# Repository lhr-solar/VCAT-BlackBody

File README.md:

# VCAT-BlackBody

Blackbody sensor boards for the LHR solar car top shell (VCAT / Telemetry).

Measures **solar irradiance** and **solar-module temperature** at locations across the top shell and reports them over CAN.

## Boards

| Board | Folder | Purpose |
|---|---|---|
| Main board | `hardware/` (`BlackBodyBoard.kicad_pro`) | Collects sensor data from the breakout(s), does the math, sends CAN messages |
| Breakout board | `hardware/IrradianceBreakout` | Holds the irradiance and temperature sensors on the top shell |

Baseline quantity: 3 (final count and placement TBD).

## CAN data (planned)

| Message | Rate |
|---|---|
| Solar irradiance (W/m²) | 10 Hz |
| Solar-module temperature (°C) | 2 Hz |
| Board status / faults | 1 Hz |

## Repo layout

Same layout as VCAT-StrainGaugeBoard:

```
CubeMX/CubeMX.ioc               STM32G473 pin/clock config (started from strain gauge; re-pin for Blackbody)
hardware/BlackBodyBoard.*        main board project (root sheet)
hardware/<Block>.kicad_sch       design blocks: PowerProtection, 12VBuck, Power_Mux, LDO,
                                 USB-C_Connector, 48PinMCU, CAN_Transceiver,
                                 Irradiance, Thermocouple, TC_Channel
hardware/IrradianceBreakout/     sensor breakout project
lib/KiCAD-Sharepoint/            shared LHRS symbols, footprints, design blocks (submodule)
lib/footprints/, lib/3dmodels/   board-specific parts
```

Conventions: power symbols + local labels on the root sheet, hierarchical labels inside sub-sheets, inputs on the left / outputs on the right, passive values without units (`10k`, `0.1u`).

## Getting started

```sh
git clone https://github.com/lhr-solar/VCAT-BlackBody.git
cd VCAT-BlackBody
git submodule update --init --recursive
```

## Documentation

Requirements: VCAT Board Tracker → Blackbody Board (Notion).

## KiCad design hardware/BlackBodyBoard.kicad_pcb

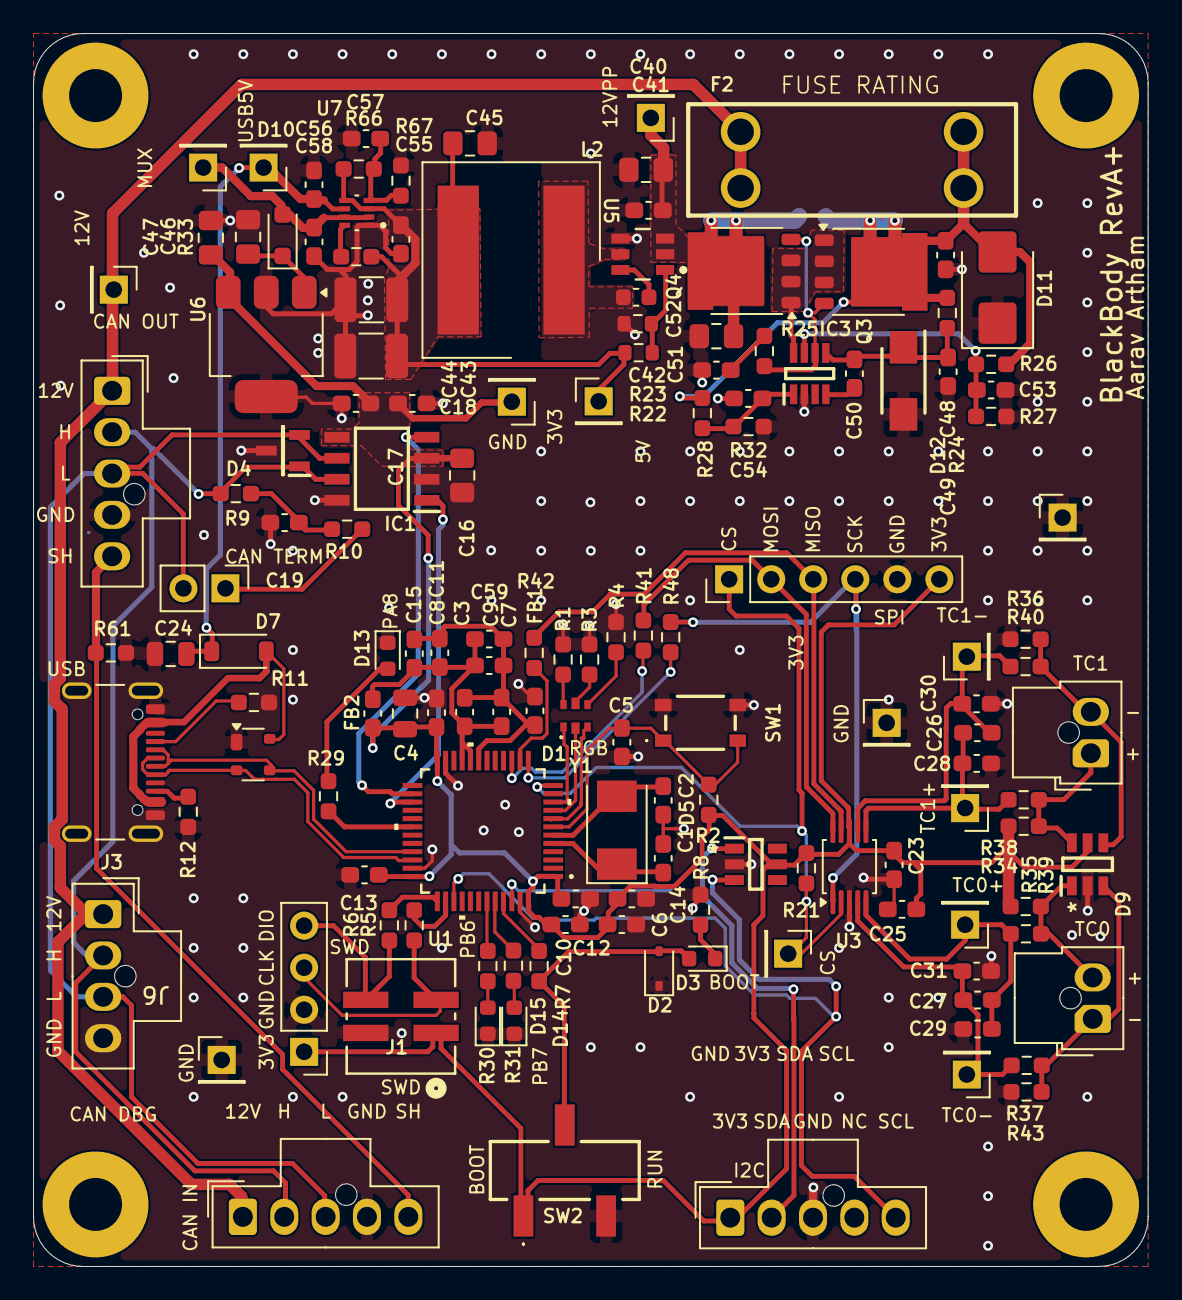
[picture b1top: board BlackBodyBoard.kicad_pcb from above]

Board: 2 copper layers, 67.3 x 74.5 mm, 147 parts (1 on the bottom side), 74 nets.

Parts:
C1, C2: 26p; C_0603_1608Metric_Pad1.08x0.95mm_HandSolder
C3, C5, C6, C7, C8, C10, C12, C13, C14, C17, C18, C19, C48, C53, C54, C55, C56, C57, C58: 0.1u; C_0603_1608Metric_Pad1.08x0.95mm_HandSolder
C4, C24: 10u; C_0805_2012Metric
C9, C11, C25, C49: 1u; C_0603_1608Metric_Pad1.08x0.95mm_HandSolder
C15, C23, C26, C27, C41: 100n; C_0603_1608Metric_Pad1.08x0.95mm_HandSolder
C16, C46, C47, C52: 10u; C_0805_2012Metric_Pad1.18x1.45mm_HandSolder
C28, C29, C30, C31, C51: 10n; C_0603_1608Metric_Pad1.08x0.95mm_HandSolder
C40: 4.7u; C_0805_2012Metric_Pad1.18x1.45mm_HandSolder
C42: 100n; C_0603_1608Metric
C43, C44: 22u; C_1210_3225Metric_Pad1.33x2.70mm_HandSolder
C45: 3.3u; C_0805_2012Metric_Pad1.18x1.45mm_HandSolder
C50: 220n; C_0603_1608Metric_Pad1.08x0.95mm_HandSolder
C59: 10u; C_0603_1608Metric_Pad1.08x0.95mm_HandSolder
D1: RGB_LED
D2: TVS; D_SOD-323
D3, D13, D14, D15: LED; LED_0603_1608Metric
D4: CDSOT23-T24CAN
D5, D9: D5V0P4UR6SO-7
D6: SP0503BAHT; SOT-143
D7: D_Schottky; D_SOD-123
D10: SBA130CH-AU_R1_000A1; D_SOD-323_HandSoldering
D11: SMBJ15CA; D_SMB
D12: SMAF4758A; SODFL5026X125N
F2: Fuse; Fuse-3557-2
FB1, FB2: FerriteBead; C_0603_1608Metric_Pad1.08x0.95mm_HandSolder
H1, H2, H3, H4: MountingHole_3.2mm_M3_Pad
IC1: TCAN3413DR
IC3: LM74502DDFR
J1: SWD_Header; SWD_Conn
J2: SWD; PinHeader_1x04_P2.54mm_Vertical
J3: USB_C_Receptacle_USB2.0_16P; USB_C_Receptacle_GCT_USB4105-xx-A_16P_TopMnt_Horizontal
J4: Nano-Fit 1x5; Molex_Nano-Fit_105309-xx05_1x05_P2.50mm_Vertical
J5, J8: TC K-type; Molex_Nano-Fit_105309-xx02_1x02_P2.50mm_Vertical
J6: CAN_DEBUG; Molex_Nano-Fit_105309-xx04_1x04_P2.50mm_Vertical
J7: CAN_IN; Molex_Nano-Fit_105309-xx05_1x05_P2.50mm_Vertical
J10: SPI; PinHeader_1x06_P2.54mm_Vertical
J11: CAN_OUT; Molex_Nano-Fit_105309-xx05_1x05_P2.50mm_Vertical
JP1: TRM; PinHeader_1x02_P2.54mm_Vertical
JP3: SolderJumper_2_Open; SolderJumper-2_P1.3mm_Open_RoundedPad1.0x1.5mm
L2: 8.2u; 74439369082
Q3, Q4: PSMN012-100YS; LFPAK56
R1, R3, R4, R8, R29, R30, R31, R38, R39, R40, R43: 1k; R_0603_1608Metric_Pad0.98x0.95mm_HandSolder
R2, R7, R21, R24, R33: 10k; R_0603_1608Metric_Pad0.98x0.95mm_HandSolder
R5, R6, R41, R42, R48: 22; R_0603_1608Metric_Pad0.98x0.95mm_HandSolder
R9, R10: 60; R_0603_1608Metric_Pad0.98x0.95mm_HandSolder
R11, R12: 5.1k; R_0603_1608Metric_Pad0.98x0.95mm_HandSolder
R22: 100k; R_0603_1608Metric
R23: 19.1k; R_0603_1608Metric
R25: 33; R_0603_1608Metric_Pad0.98x0.95mm_HandSolder
R26, R28: 100k; R_0603_1608Metric_Pad0.98x0.95mm_HandSolder
R27: 7.32k; R_0603_1608Metric_Pad0.98x0.95mm_HandSolder
R32: 15.8k; R_0603_1608Metric_Pad0.98x0.95mm_HandSolder
R34, R35, R36, R37: 1M; R_0603_1608Metric_Pad0.98x0.95mm_HandSolder
R61: 0; R_0603_1608Metric_Pad0.98x0.95mm_HandSolder
R66: 16k; R_0603_1608Metric_Pad0.98x0.95mm_HandSolder
R67: 4.7k; R_0603_1608Metric_Pad0.98x0.95mm_HandSolder
SW1: Reset; TL3365AF180QG
SW2: SW_SPDT; BootSW
TP6: TC_ADC_CS; PinHeader_1x01_P2.54mm_Vertical
TP7, TP8: TCP; PinHeader_1x01_P2.54mm_Vertical
TP10, TP11: TCN; PinHeader_1x01_P2.54mm_Vertical
TP38: +12V; PinHeader_1x01_P2.54mm_Vertical
TP39: +12V_PP; PinHeader_1x01_P2.54mm_Vertical
TP40: +5V_BUCK; PinHeader_1x01_P2.54mm_Vertical
TP41: +USBC_5V; PinHeader_1x01_P2.54mm_Vertical
TP42: MUX_OUT; PinHeader_1x01_P2.54mm_Vertical
TP44: Power TestPoint; PinHeader_1x01_P2.54mm_Vertical
TP45: MCU TestPoint; PinHeader_1x01_P2.54mm_Vertical
TP46: CAN TestPoint; PinHeader_1x01_P2.54mm_Vertical
TP_3.3V2: 3.3V; PinHeader_1x01_P2.54mm_Vertical
U1: STM32G473CETx; 48PinMCU
U3: ADS1118IDGS; TSSOP-10_3x3mm_P0.5mm
U5: LMR51635XDDCR; DDC0006A-MFG
U6: MCP1826S; SOT-223-3_TabPin2
U7: TPS2117DRLR
Y1: Crystal; Crystal_SMD_Abracon_ABM3-2Pin_5.0x3.2mm

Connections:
+3.3V: C4.1, C6.1, C8.1, C10.1, C12.1, C13.1, C14.1, C16.1, C17.1, C18.1, C23.1, C25.1, C47.2, D5.5, D9.5, FB2.1, IC1.3 (VCC), IC1.5 (SHDNV_IO), J1.1, J2.1, J4.1, J10.6, R2.2, R21.1, R34.1, R35.1, SW2.1 (A), TP_3.3V2.1 (1_1), U1.1 (VBAT), U1.24 (VDD), U1.36 (VDD), U1.48 (VDD), U3.8 (VDD), U6.3 (VO)
+12V: F2.1, J6.1 (12V), J7.1 (12V), J11.1 (12V), TP38.1 (1_1)
/12VBuck1/CB: C42.1, U5.6 (CB)
/12VBuck1/FB: R22.2, R23.1, U5.1 (FB)
/12VBuck1/SW: C42.2, L2.1, U5.5 (SW)
/48PinMCU/BOOT0: R7.1, U1.45 (PB8-BOOT0)
/48PinMCU/NRST: C5.1, R2.1, SW1.1, U1.7 (PG10-NRST)
/48PinMCU/PA0: D1.5, U1.8 (PA0-GPIO_BLUE)
/48PinMCU/PA1: D1.3, U1.9 (PA1_GPIO_RED)
/48PinMCU/PA2: D1.1, U1.10 (PA2-GPIO_GREEN)
/48PinMCU/PA5: R48.1, U1.13 (PA5)
/48PinMCU/PA6: R42.1, U1.14 (PA6)
/48PinMCU/PA7: R41.1, U1.15 (PA7)
/48PinMCU/PA8: R29.1, U1.30 (PA8)
/48PinMCU/PB6: R30.1, U1.43 (PB6)
/48PinMCU/PB7: R31.1, U1.44 (PB7)
/48PinMCU/SWCLK: R5.1, U1.38 (PA14)
/48PinMCU/SWDIO: R6.1, U1.37 (PA13)
/48PinMCU/USB_DM: D6.3 (K), J3.A7 (D-), J3.B7 (D-), U1.33 (PA11)
/48PinMCU/USB_DP: D6.2 (K), J3.A6 (D+), J3.B6 (D+), U1.34 (PA12)
/48PinMCU/VDDA: C3.1, C7.1, C9.1, C11.1, C15.1, C59.1, FB2.2, U1.20 (VREF+), U1.21 (VDDA)
/+5V_BUCK: C43.1, C44.1, C45.1, C55.1, L2.2, R22.1, R33.1, R66.1, TP40.1 (1_1), U7.3 (VIN1), U7.5 (MODE)
/+12V_PP: C40.1, C41.1, C52.1, JP3.2 (B), Q4.5, TP39.1 (1_1), U5.2 (EN), U5.3 (VIN)
/+USBC_5V: C24.2, C56.1, D7.1 (K), TP41.1 (1_1), U7.6 (VIN2)
/CAN_H: D4.1 (CAN_H), IC1.7 (CANH), J6.2 (CAN_H), J7.2 (CAN_H), J11.2 (CAN_H), R9.1
/CAN_L: D4.2 (CAN_L), IC1.6 (CANL), J6.3 (CAN_L), J7.3 (CAN_L), J11.3 (CAN_L), JP1.2 (B)
/CAN_RX: IC1.4 (RXD), U1.26 (PB12)
/CAN_SHIELD: J7.5 (SHIELD), J11.5 (SHIELD), R61.1
/CAN_TX: IC1.1 (TXD), U1.27 (PB13)
/I2C_SCL: D5.3, J4.5, U1.39 (PA15)
/I2C_SDA: D5.1, J4.2, U1.46 (PB9)
/MUX_OUT: C58.1, D10.2 (A), TP42.1 (1_1), U7.2 (VOUT), U7.7 (VOUT__1)
/PowerProtection1/EN/UVLO: C54.1, IC3.1 (EN/UVLO), R28.2, R32.2
/PowerProtection1/OV: C53.1, IC3.7 (OV), R26.2, R27.1
/PowerProtection1/Vin: C48.1, D11.2 (A2), F2.2, JP3.1 (A), Q3.5, R24.2, R26.1, R28.1
/PowerProtection1/gate: IC3.6 (GATE), Q3.4, Q4.4, R25.2
/PowerProtection1/source: IC3.8 (SRC), Q3.1, Q3.2, Q3.3, Q4.1, Q4.2, Q4.3
/Power_Mux1/PR1: C57.1, R66.2, R67.1, U7.4 (PR1)
/SPI_MISO: J10.3, R42.2, U3.9 (DOUT/~DRDY)
/SPI_MOSI: J10.2, R41.2, U3.10 (DIN)
/SPI_SCK: J10.4, R48.2, U3.1 (SCLK)
/TC_ADC_CS: J10.1, R21.2, TP6.1 (1_1), U1.12 (PA4), U3.2 (~CS)
/Thermocouple/TC0+: D9.1, J8.2, R35.2, R39.1
/Thermocouple/TC0-: D9.3, J8.1, R37.1, R43.1
/Thermocouple/TC0N: C27.2, C31.1, R43.2, TP11.1 (1_1), U3.4 (AIN0)
/Thermocouple/TC0P: C27.1, C29.1, R39.2, TP8.1 (1_1), U3.5 (AIN1)
/Thermocouple/TC1+: D9.6, J5.1, R34.2, R38.1
/Thermocouple/TC1-: D9.4, J5.2, R36.1, R40.1
/Thermocouple/TC1N: C26.2, C30.1, R40.2, TP10.1 (1_1), U3.7 (AIN3)
/Thermocouple/TC1P: C26.1, C28.1, R38.2, TP7.1 (1_1), U3.6 (AIN2)
/USB-C_Connector/CC1: J3.A5 (CC1), R11.2
/USB-C_Connector/CC2: J3.B5 (CC2), R12.2
/USB-C_Connector/VBUS_IN: D6.4 (K), D7.2 (A), J3.A4 (VBUS), J3.A9 (VBUS), J3.B4 (VBUS), J3.B9 (VBUS)
GND: C1.1, C2.2, C4.2, C5.2, C6.2, C8.2, C10.2, C12.2, C13.2, C14.2, C16.2, C17.2, C18.2, C19.1, C23.2, C24.1, C25.2, C28.2, C29.2, C30.2, C31.2, C40.2, C41.2, C43.2, C44.2, C45.2, C46.1, C47.1, C48.2, C49.1, C51.2, C52.2, C53.2, C54.2, C55.2, C56.2, C57.2, C58.2, D2.1 (A1), D4.3 (GND), D5.2, D6.1 (A), D9.2, D11.1 (A1), D12.2 (A), D13.1 (K), D14.1 (K), D15.1 (K), FB1.2, IC1.2 (GND), IC1.8 (STB), IC3.2 (GND), J1.2, J2.2, J3.A1 (GND), J3.A12 (GND), J3.B1 (GND), J3.B12 (GND), J3.S1 (SHIELD), J3.S2 (Shield), J3.S3 (Shield), J3.S4 (Shield), J4.3, J6.4 (GND), J7.4 (GND), J10.5, J11.4 (GND), R1.2, R3.2, R4.2, R8.2, R11.1, R12.1, R23.2, R27.2, R32.1, R36.2, R37.2, R61.2, R67.2, SW1.2, SW2.3 (C), TP44.1 (1_1), TP45.1 (1_1), TP46.1 (1_1), U1.23 (VSS), U1.35 (VSS), U1.47 (VSS), U3.3 (GND), U5.4 (GND), U6.2 (GND), U7.1 (GND)
GNDA: C3.2, C7.2, C9.2, C11.2, C15.2, C59.2, FB1.1, U1.19 (VSSA)
unnamed: C19.2, R9.2, R10.1
unnamed: C51.1, R25.1
unnamed: D1.2, R1.1
unnamed: D1.4, R3.1
unnamed: D1.6, R4.1
unnamed: D2.2 (A2), D3.2 (A), R7.2, SW2.2 (B)
unnamed: D3.1 (K), R8.1
unnamed: C46.2, D10.1 (K), U6.1 (VI)
unnamed: C49.2, C50.1, D12.1 (K), IC3.5 (VS), R24.1
unnamed: D13.2 (A), R29.2
unnamed: D14.2 (A), R30.2
unnamed: D15.2 (A), R31.2
unnamed: C50.2, IC3.4 (VCAP)
unnamed: J1.3, J2.3, R5.2
unnamed: J1.4, J2.4, R6.2
unnamed: JP1.1 (A), R10.2
unnamed: C1.2, U1.5 (PF0-OSC_IN), Y1.1
unnamed: C2.1, U1.6 (PF1-OSC_OUT), Y1.2
unnamed: R33.2, U7.8 (ST)

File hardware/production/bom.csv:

Designator,Footprint,Quantity,Value,LCSC Part #
"C1, C2",0603,2,26p,C92670
"C10, C12, C13, C14, C17, C18, C19, C3, C5, C6, C7, C8",0603,12,0.1u,C14663
"C11, C25, C9",0603,3,1u,C15849
C15,0603,1,100n,C15849
"C16, C24, C4, C46, C47, C52",0805,6,10u,C440198
"C23, C26, C27",0603,3,100n,C1591
"C28, C29, C30, C31, C51",0603,5,10n,C100042
C40,0805,1,4.7u,C6962403
"C41, C42",0603,2,100n,C6666325
"C43, C44",1210,2,22u,C778721
C45,0805,1,3.3u,C342775
"C48, C53, C54",0603,3,0.1u,C1591
C49,0603,1,1u,C559769
C50,0603,1,220n,C107083
"C55, C56, C57, C58",0603,4,0.1u,
C59,0603,1,10u,C15849
D1,RGB_LED,1,RGB_LED,C264519
D10,D_SOD-323_HandSoldering,1,SBA130CH-AU_R1_000A1,C191023
D11,D_SMB,1,SMBJ15CA,C669039
D12,SODFL5026X125N,1,SMAF4758A,C183490
"D13, D14, D15, D3",0603,4,LED,C125103
D2,D_SOD-323,1,TVS,C725495
D4,CDSOT23-T24CAN,1,CDSOT23-T24CAN,C2959841
"D5, D9",D5V0P4UR6SO-7,2,D5V0P4UR6SO-7,
D6,SOT-143,1,SP0503BAHT,C7074
D7,D_SOD-123,1,D_Schottky,C82544
F2,Fuse-3557-2,1,Fuse,C352820
"FB1, FB2",0603,2,FerriteBead,C354394
IC1,TCAN3413DR,1,TCAN3413DR,C22433320
IC3,LM74502DDFR,1,LM74502DDFR,C3236215
J1,SWD_Conn,1,SWD_Header,C17492485
J10,PinHeader_1x06_P2.54mm_Vertical,1,SPI,
J11,Molex_Nano-Fit_105309-xx05_1x05_P2.50mm_Vertical,1,CAN_OUT,
J2,PinHeader_1x04_P2.54mm_Vertical,1,SWD,
J3,USB_C_Receptacle_GCT_USB4105-xx-A_16P_TopMnt_Horizontal,1,USB_C_Receptacle_USB2.0_16P,C3020560
J4,Molex_Nano-Fit_105309-xx05_1x05_P2.50mm_Vertical,1,Nano-Fit 1x5,
"J5, J8",Molex_Nano-Fit_105309-xx02_1x02_P2.50mm_Vertical,2,TC K-type,
J6,Molex_Nano-Fit_105309-xx04_1x04_P2.50mm_Vertical,1,CAN_DEBUG,
J7,Molex_Nano-Fit_105309-xx05_1x05_P2.50mm_Vertical,1,CAN_IN,
JP1,PinHeader_1x02_P2.54mm_Vertical,1,TRM,
L2,74439369082,1,8.2u,
"Q3, Q4",LFPAK56,2,PSMN012-100YS,C20443035
"R1, R29, R3, R30, R31, R38, R39, R4, R40, R43, R8",0603,11,1k,C21190
"R10, R9",0603,2,60,C166918
"R11, R12",0603,2,5.1k,C23186
"R2, R21, R24, R7",0603,4,10k,C25804
"R22, R26, R28",0603,3,100k,C25803
R23,0603,1,19.1k,C844132
R25,0603,1,33,C2074308
R27,0603,1,7.32k,C862286
R32,0603,1,15.8k,C843918
R33,0603,1,10k,
"R34, R35, R36, R37",0603,4,1M,C22935
"R41, R42, R48, R5, R6",0603,5,22,C2930077
R61,0603,1,0,C21189
R66,0603,1,16k,C22818
R67,0603,1,4.7k,C23162
SW1,TL3365AF180QG,1,Reset,C2886926
SW2,BootSW,1,SW_SPDT,-
"TP10, TP11",PinHeader_1x01_P2.54mm_Vertical,2,TCN,
TP38,PinHeader_1x01_P2.54mm_Vertical,1,+12V,
TP39,PinHeader_1x01_P2.54mm_Vertical,1,+12V_PP,
TP40,PinHeader_1x01_P2.54mm_Vertical,1,+5V_BUCK,
TP41,PinHeader_1x01_P2.54mm_Vertical,1,+USBC_5V,
TP42,PinHeader_1x01_P2.54mm_Vertical,1,MUX_OUT,
TP44,PinHeader_1x01_P2.54mm_Vertical,1,Power TestPoint,
TP45,PinHeader_1x01_P2.54mm_Vertical,1,MCU TestPoint,
TP46,PinHeader_1x01_P2.54mm_Vertical,1,CAN TestPoint,
TP6,PinHeader_1x01_P2.54mm_Vertical,1,TC_ADC_CS,
"TP7, TP8",PinHeader_1x01_P2.54mm_Vertical,2,TCP,
U1,48PinMCU,1,STM32G473CETx,C730113
U3,TSSOP-10_3x3mm_P0.5mm,1,ADS1118IDGS,C55347
U5,DDC0006A-MFG,1,LMR51635XDDCR,
U6,SOT-223-3_TabPin2,1,MCP1826S,C126055
U7,TPS2117DRLR,1,TPS2117DRLR,
Y1,Crystal_SMD_Abracon_ABM3-2Pin_5.0x3.2mm,1,Crystal,C144380

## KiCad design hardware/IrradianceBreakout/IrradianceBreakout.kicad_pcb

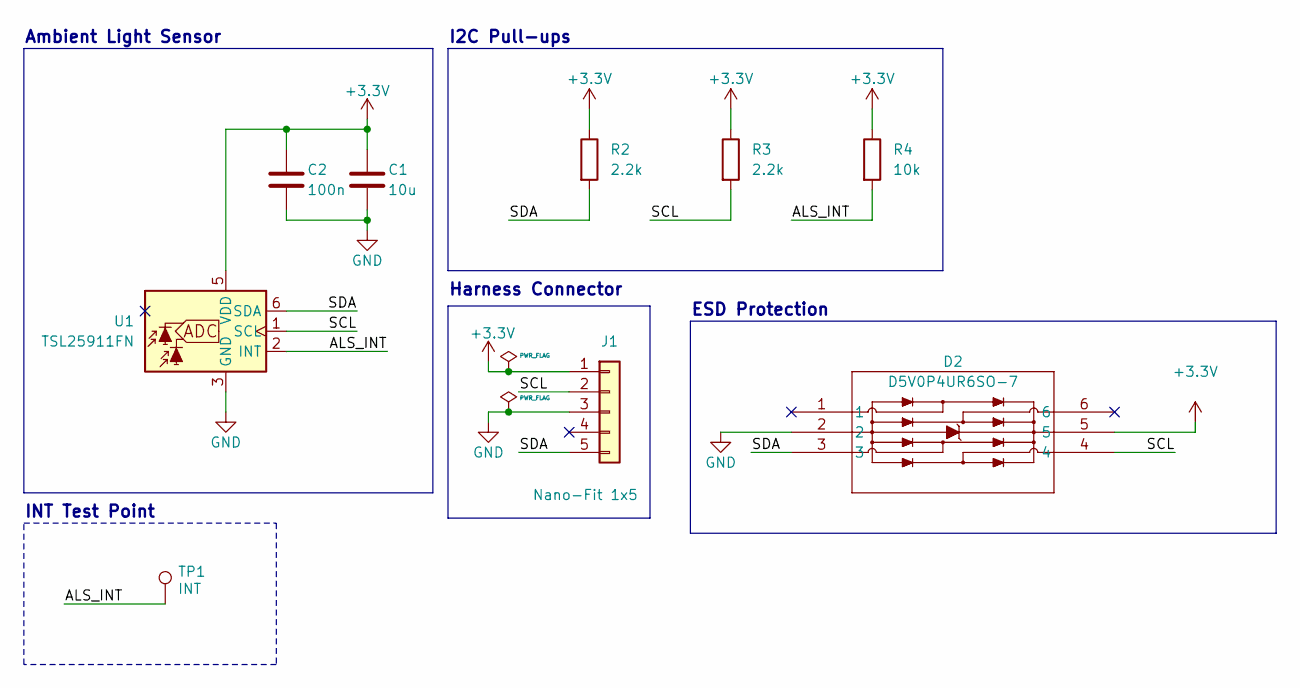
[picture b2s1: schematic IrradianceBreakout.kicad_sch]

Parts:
C1: 10u; C_0805_2012Metric_Pad1.18x1.45mm_HandSolder
C2: 100n; C_0603_1608Metric_Pad1.08x0.95mm_HandSolder
D2: D5V0P4UR6SO-7; Mouser Part Number 621-D5V0P4UR6SO-7
J1: Nano-Fit 1x5; Molex_Nano-Fit_105313-xx05_1x05_P2.50mm_Horizontal
R2, R3: 2.2k; R_0603_1608Metric_Pad0.98x0.95mm_HandSolder; LCSC P/N C4190
R4: 10k; R_0603_1608Metric_Pad0.98x0.95mm_HandSolder; LCSC P/N C25804
TP1: INT; TestPoint_Pad_D1.5mm
U1: TSL25911FN; AMS_TSL25911FN; LCSC P/N C176812

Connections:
+3.3V: C1.1, C2.1, D2.5, J1.1, R2.1, R3.1, R4.1, U1.5 (VDD)
/ALS_INT: R4.2, TP1.1, U1.2 (INT)
/SCL: D2.4, J1.2, R3.2, U1.1 (SCL)
/SDA: D2.3, J1.5, R2.2, U1.6 (SDA)
GND: C1.2, C2.2, D2.2, J1.3, U1.3 (GND)

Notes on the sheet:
INT Test Point
I2C Pull-ups
Ambient Light Sensor
ESD Protection
Harness Connector

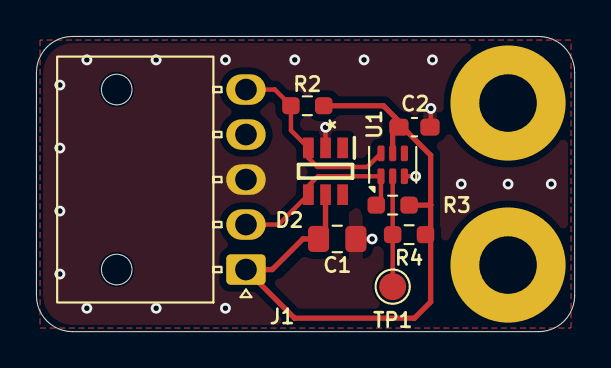
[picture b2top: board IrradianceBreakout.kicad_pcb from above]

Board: 2 copper layers, 29.9 x 16.4 mm, 11 parts (0 on the bottom side), 5 nets.

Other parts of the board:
H1, H2: MountingHole_3.2mm_M3_Pad

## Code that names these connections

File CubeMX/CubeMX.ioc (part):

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Mcu.Name=STM32G473C(B-C-E)Tx
Mcu.Package=LQFP48
Mcu.UserName=STM32G473CETx
PA0.GPIOParameters=GPIO_Label
PA0.GPIO_Label=LED_B
PA0.Signal=S_TIM2_CH1
PA1.GPIOParameters=GPIO_Label
PA1.GPIO_Label=LED_R
PA1.Signal=S_TIM2_CH2
PA10.GPIOParameters=GPIO_PuPd,GPIO_Label,GPIO_ModeDefaultEXTI
PA10.GPIO_Label=IRRAD_INT
PA10.GPIO_ModeDefaultEXTI=GPIO_MODE_IT_FALLING
PA10.GPIO_PuPd=GPIO_NOPULL
PA10.Signal=GPXTI10
PA11.Mode=Device
PA11.Signal=USB_DM
PA12.Mode=Device
PA12.Signal=USB_DP
PA13.Mode=Serial_Wire
PA13.Signal=SYS_JTMS-SWDIO
PA14.Mode=Serial_Wire
PA14.Signal=SYS_JTCK-SWCLK
PA15.Mode=I2C
PA15.Signal=I2C1_SCL
PA2.GPIOParameters=GPIO_Label
PA2.GPIO_Label=LED_G
PA2.Signal=S_TIM2_CH3
PA4.GPIOParameters=PinState,GPIO_Label
PA4.GPIO_Label=TC_ADC_CS
PA4.PinState=GPIO_PIN_SET
PA4.Signal=GPIO_Output
PA5.Mode=Full_Duplex_Master
PA5.Signal=SPI1_SCK
PA6.Mode=Full_Duplex_Master
PA6.Signal=SPI1_MISO
PA7.Mode=Full_Duplex_Master
PA7.Signal=SPI1_MOSI
PA8.GPIOParameters=GPIO_Label
PA8.GPIO_Label=STATUS_LED1
PA8.Signal=GPIO_Output
PB12.GPIOParameters=GPIO_Label
PB12.GPIO_Label=CAN_RX
PB12.Mode=FDCAN_Activate
PB12.Signal=FDCAN2_RX
PB13.GPIOParameters=GPIO_Label
PB13.GPIO_Label=CAN_TX
PB13.Mode=FDCAN_Activate
PB13.Signal=FDCAN2_TX
PB6.GPIOParameters=GPIO_Label
PB6.GPIO_Label=STATUS_LED2
PB6.Signal=GPIO_Output
PB7.GPIOParameters=GPIO_Label
PB7.GPIO_Label=STATUS_LED3
PB7.Signal=GPIO_Output
PB9.Mode=I2C
PB9.Signal=I2C1_SDA
PF0-OSC_IN.Mode=HSE-External-Oscillator
PF0-OSC_IN.Signal=RCC_OSC_IN
PF1-OSC_OUT.Mode=HSE-External-Oscillator
PF1-OSC_OUT.Signal=RCC_OSC_OUT
RCC.HSE_VALUE=8000000
RCC.SYSCLKFreq_VALUE=16000000
board=custom
